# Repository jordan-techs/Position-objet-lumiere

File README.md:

# Positionnement d’un objet à l’aide de sources lumineuses

Ce projet vise à localiser un objet dans un espace en exploitant des sources lumineuses fixes (LEDs) et des capteurs de lumière placés sur l’objet. L’objectif est de déterminer la position de l’objet en temps réel, à l’aide de mesures d’intensité lumineuse et de calculs de triangulation.

## 🎯 Objectifs
- Utiliser plusieurs sources lumineuses fixes 
- Capturer l’intensité lumineuse avec des photodiodes ou capteur de lumière
- Estimer la position de l’objet par triangulation ou modulation de la fréquence des sources
- calcul de la position estimée en temps réel avec carte FPGA

## ⚙️ Technologies & Matériel utilisés
- Photodiodes / capteurs lumière
- LEDs fixes (IR ou blanches)
- Carte FPGA (Terasic DE1-SoC)
- Logiciel quartus 2
- vhdl pour l’embarqué
- simulation de l'acquisitions d’images avec Python

## 🧠 Fonctionnement
- Plusieurs LEDs sont disposées dans l’environnement.
- L’objet mobile est équipé de photodiodes ou capteurs de lumière.
- En mesurant l’intensité perçue de chaque LED, on estime la position de l’objet.
- Traitement des données à l'aide de la FPGA

## 📷 Démo (à compléter si tu as une image ou vidéo)
Ajoute ici une image du montage ou un lien vers une vidéo (YouTube, Drive, etc.)

## 📦 Structure du code

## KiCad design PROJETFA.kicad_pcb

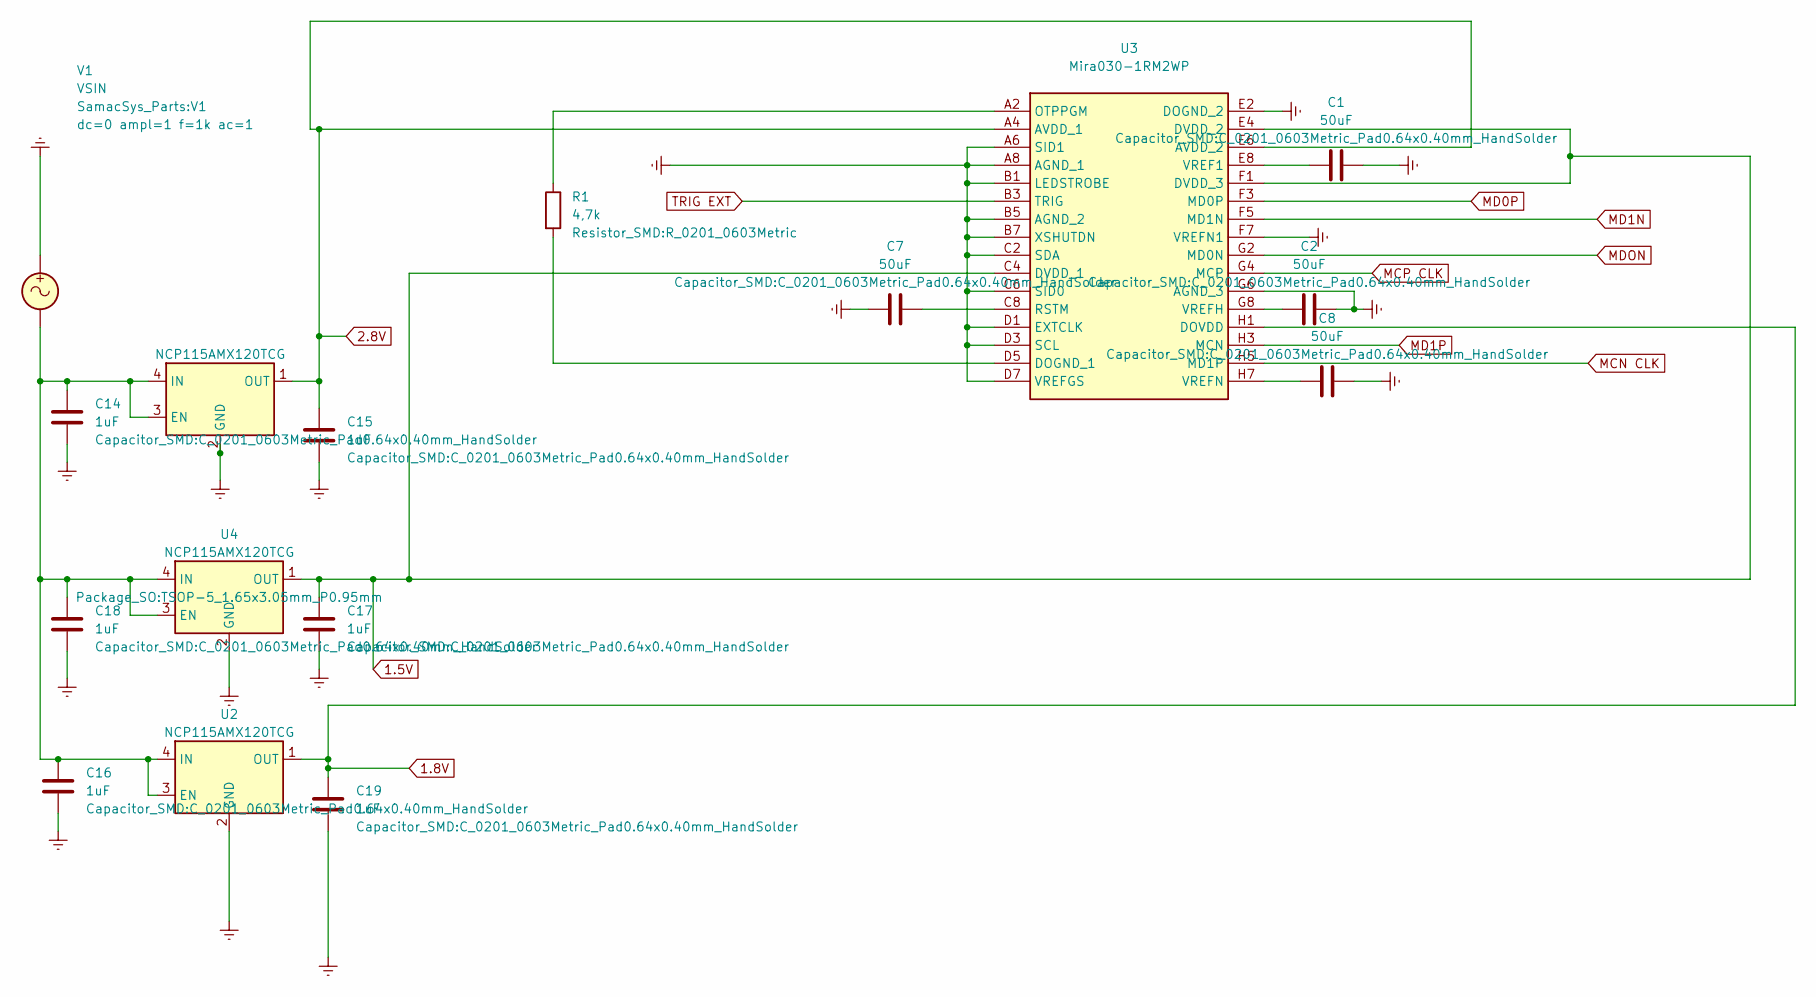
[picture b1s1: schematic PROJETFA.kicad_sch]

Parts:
C1, C2, C7, C8: 50uF; C_0201_0603Metric_Pad0.64x0.40mm_HandSolder
C14, C15, C16, C17, C18, C19: 1uF; C_0201_0603Metric_Pad0.64x0.40mm_HandSolder
R1: 4,7k; R_0201_0603Metric
U1, U2, U4: NCP115AMX120TCG; TSOP-5_1.65x3.05mm_P0.95mm
U3: Mira030-1RM2WP; Mira0301RM2WP; Manufacturer_Part_Number Mira030-1RM2WP; Mouser Part Number 985-MIRA030-1RM2WP
V1: VSIN; V1

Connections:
1.5V: C17.2, U3.C4 (DVDD_1), U3.E4 (DVDD_2), U3.F1 (DVDD_3), U4.1 (OUT)
1.8V: C19.2, U2.1 (OUT), U3.H1 (DOVDD)
2.8V: C15.2, U1.1 (OUT), U3.A4 (AVDD_1), U3.E6 (AVDD_2)
Earth: C1.1, C2.2, C7.2, C8.2, C14.1, C15.1, C16.1, C17.1, C18.1, C19.1, U1.2 (GND), U1.5 (GND), U2.2 (GND), U2.5 (GND), U3.A6 (SID1), U3.A8 (AGND_1), U3.B1 (LEDSTROBE), U3.B5 (AGND_2), U3.B7 (XSHUTDN), U3.C2 (SDA), U3.C6 (SID0), U3.D1 (EXTCLK), U3.D3 (SCL), U3.D7 (VREFGS), U3.E2 (DOGND_2), U3.F7 (VREFN1), U3.G6 (AGND_3), U4.2 (GND), U4.5 (GND), V1.1
MCN CLK: U3.H5 (MD1P)
MCP CLK: U3.G4 (MCP)
MD0P: U3.F3 (MD0P)
MD1N: U3.F5 (MD1N)
MD1P: U3.H3 (MCN)
MDON: U3.G2 (MD0N)
unnamed: C14.2, C16.2, C18.2, U1.3 (EN), U1.4 (IN), U2.3 (EN), U2.4 (IN), U4.3 (EN), U4.4 (IN), V1.2
unnamed: R1.2, U3.D5 (DOGND_1)
unnamed: R1.1, U3.A2 (OTPPGM)
unnamed: C7.1, U3.C8 (RSTM)
unnamed: C1.2, U3.E8 (VREF1)
unnamed: C2.1, U3.G8 (VREFH)
unnamed: C8.1, U3.H7 (VREFN)
TRIG EXT: U3.B3 (TRIG)

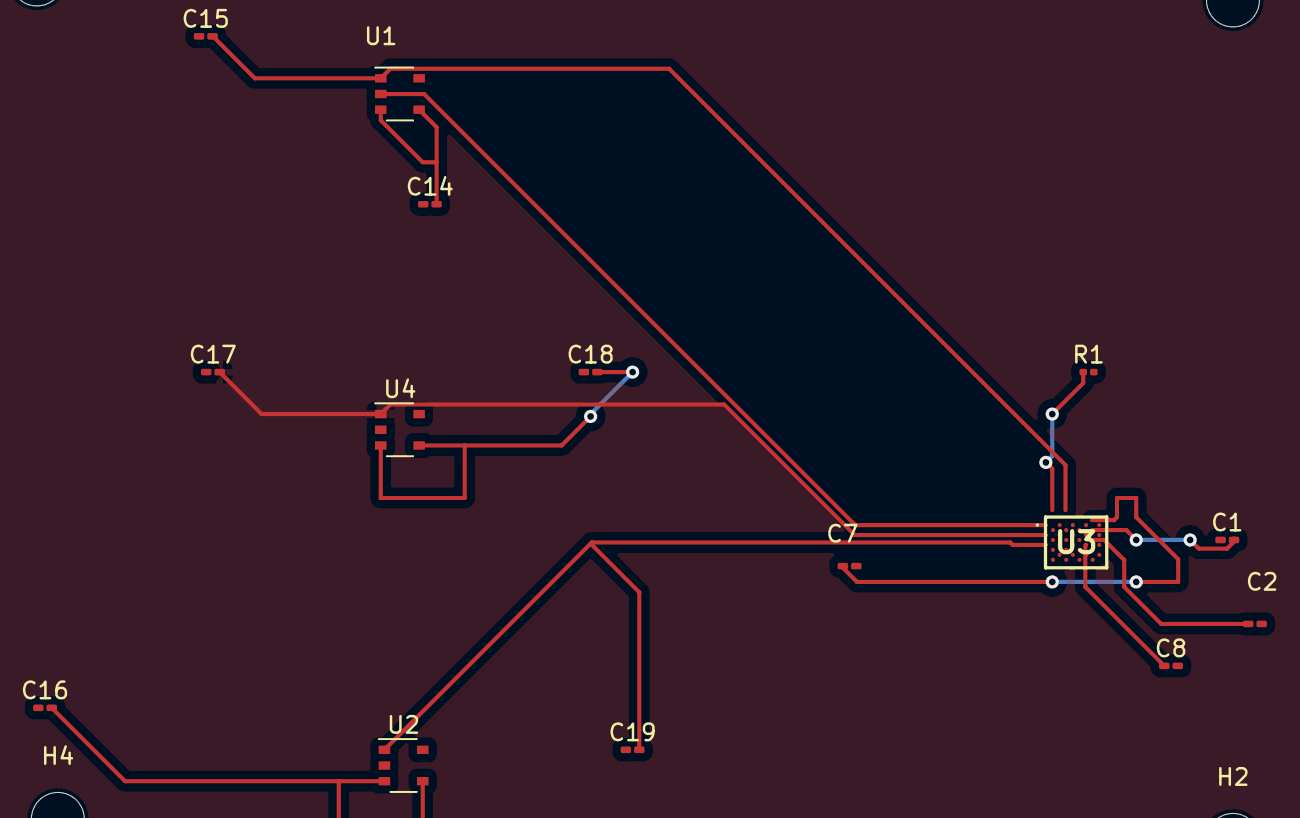
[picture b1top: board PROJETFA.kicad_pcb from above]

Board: 2 copper layers, 19 parts (0 on the bottom side), 11 nets.

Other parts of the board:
H1, H2, H3, H4: MountingHole_Pad; MountingHole_3.2mm_M3_DIN965

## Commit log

2025-04-13 Upd README.md
